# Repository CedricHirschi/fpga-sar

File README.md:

# FPGA-SAR

Material for the SAR ADC project in the **iCEBreaker FPGA For IoT Sensing Systems** FS2024 course.

## Project Description

Build a SAR ADC and a way to read its values.
- [x] Build analog part (See [hardware/](hardware/))
- [x] Develop SAR core (See [verilog/](verilog/))
- [x] Develop UART readout core (See [verilog/](verilog/))
- [ ] Optional: Evaluate speed and accuracy

## Project Structure

- [hardware/](hardware/): Contains the KiCad project for the analog part of the SAR ADC
- [verilog/](verilog/): Contains the Verilog code for the SAR ADC and UART readout core
- [gui.ipynb](gui.ipynb): Jupyter notebook for plotting the ADC values
- [activate.sh](activate.sh): Script to activate the virtual environment for development with APIO and Jupyter Notebook
- [presentation.pptx](presentation.pptx): Presentation slides for the project

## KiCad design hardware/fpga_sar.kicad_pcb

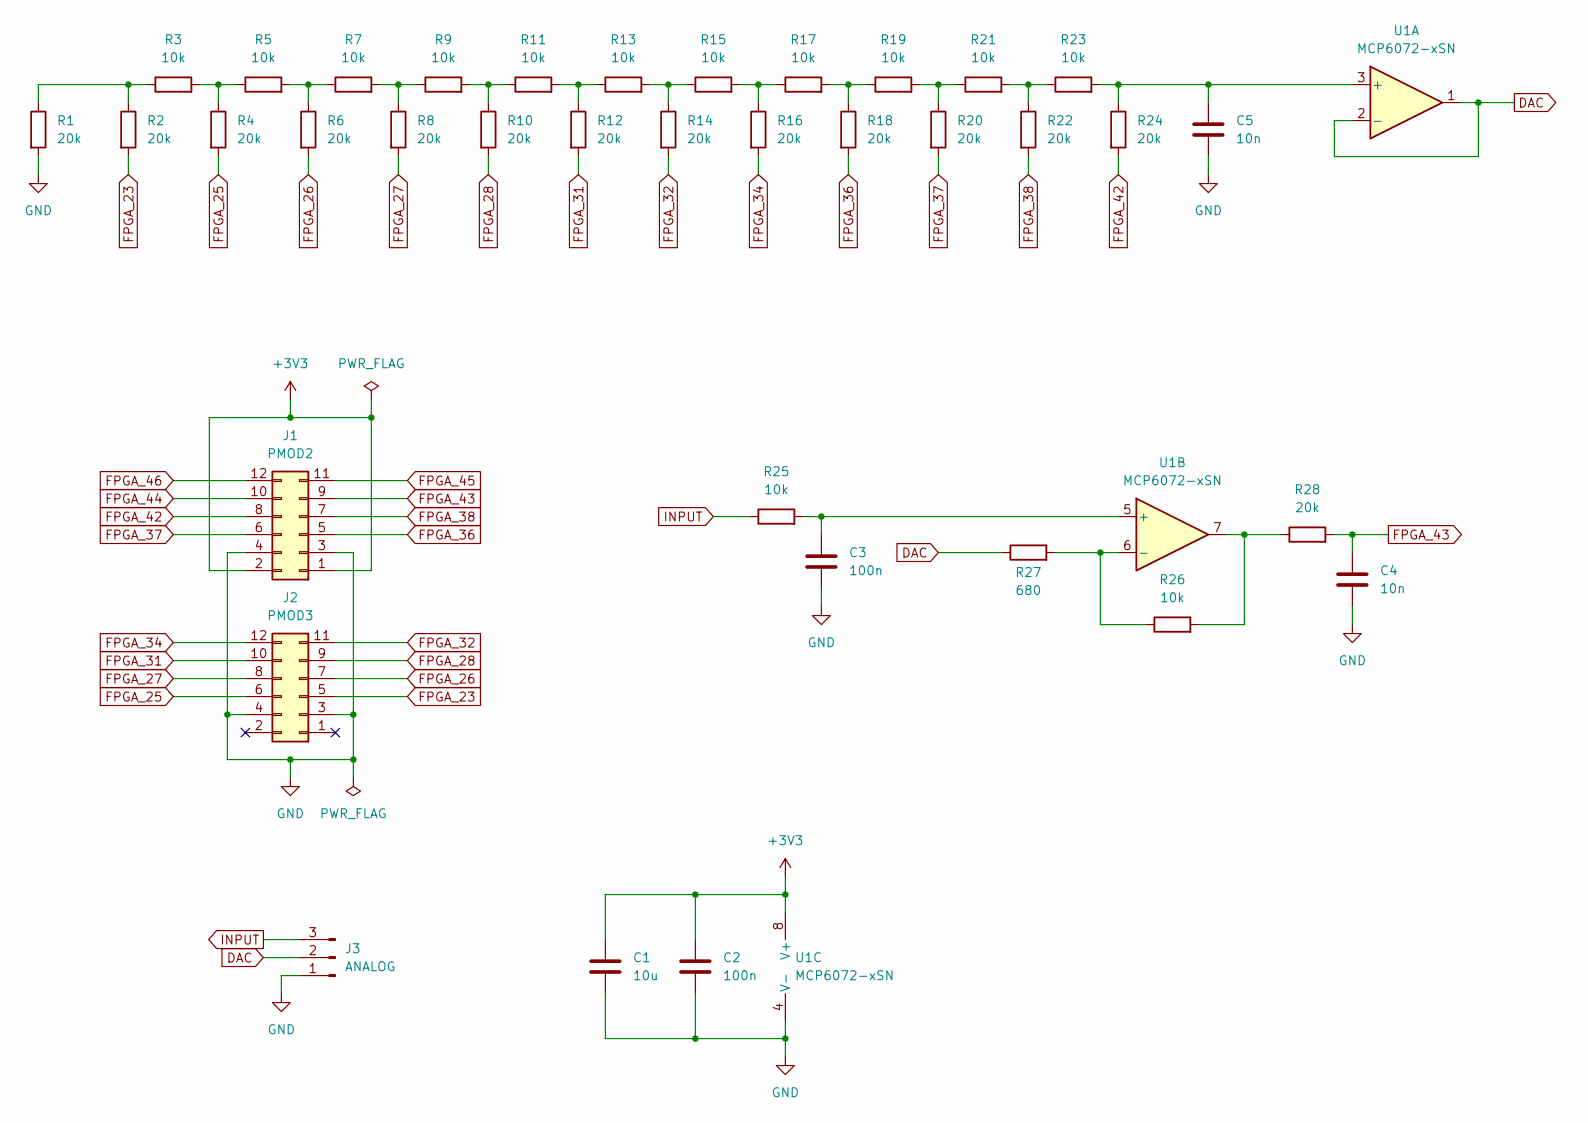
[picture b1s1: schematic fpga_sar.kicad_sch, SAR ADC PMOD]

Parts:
C1: 10u; C_0402_1005Metric
C2, C3: 100n; C_0402_1005Metric
C4, C5: 10n; C_0402_1005Metric
J1: PMOD2; PinHeader_2x06_P2.54mm_Horizontal
J2: PMOD3; PinHeader_2x06_P2.54mm_Horizontal
J3: ANALOG; PinHeader_1x03_P2.54mm_Vertical
R1, R2, R4, R6, R8, R10, R12, R14, R16, R18, R20, R22, R24, R28: 20k; R_0402_1005Metric
R3, R5, R7, R9, R11, R13, R15, R17, R19, R21, R23, R25, R26: 10k; R_0402_1005Metric
R27: 680; R_0402_1005Metric
U1: MCP6072-xSN; SOIC-8_3.9x4.9mm_P1.27mm

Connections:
+3V3: C1.1, C2.1, J1.1, J1.2, U1.8 (V+)
DAC: J3.2, R27.1, U1.1, U1.2 (-)
FPGA_23: J2.5, R2.2
FPGA_25: J2.6, R4.2
FPGA_26: J2.7, R6.2
FPGA_27: J2.8, R8.2
FPGA_28: J2.9, R10.2
FPGA_31: J2.10, R12.2
FPGA_32: J2.11, R14.2
FPGA_34: J2.12, R16.2
FPGA_36: J1.5, R18.2
FPGA_37: J1.6, R20.2
FPGA_38: J1.7, R22.2
FPGA_42: J1.8, R24.2
FPGA_43: C4.1, J1.9, R28.2
FPGA_44: J1.10
FPGA_45: J1.11
FPGA_46: J1.12
GND: C1.2, C2.2, C3.2, C4.2, C5.2, J1.3, J1.4, J2.3, J2.4, J3.1, R1.2, U1.4 (V-)
INPUT: J3.3, R25.1
unnamed: R1.1, R2.1, R3.1
unnamed: R3.2, R4.1, R5.1
unnamed: R5.2, R6.1, R7.1
unnamed: R7.2, R8.1, R9.1
unnamed: R9.2, R10.1, R11.1
unnamed: R11.2, R12.1, R13.1
unnamed: R13.2, R14.1, R15.1
unnamed: R15.2, R16.1, R17.1
unnamed: R17.2, R18.1, R19.1
unnamed: R19.2, R20.1, R21.1
unnamed: R21.2, R22.1, R23.1
unnamed: R26.2, R28.1, U1.7
unnamed: C5.1, R23.2, R24.1, U1.3 (+)
unnamed: C3.1, R25.2, U1.5 (+)
unnamed: R26.1, R27.2, U1.6 (-)

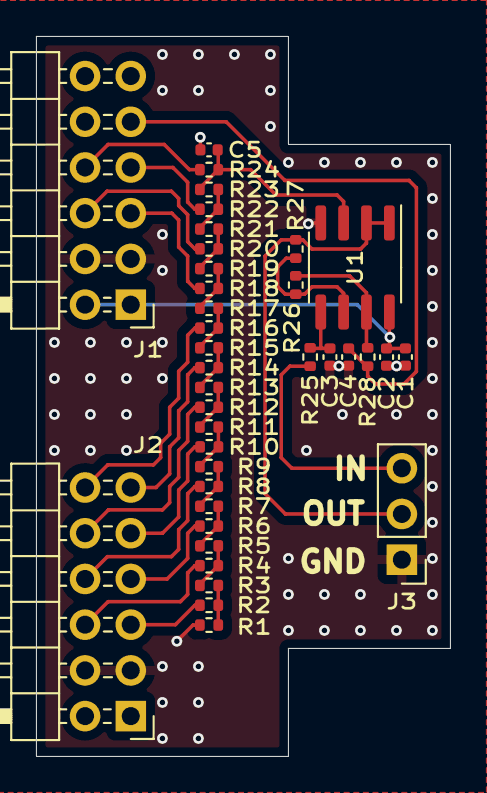
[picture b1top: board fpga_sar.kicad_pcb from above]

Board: 2 copper layers, 23.0 x 40.0 mm, 37 parts (0 on the bottom side), 32 nets.

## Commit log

2024-04-23 Initial version
    Conversion may show one below actual result
2024-04-24 Add UART readout
    Send 's' via UART 115200, 8 bits, 1 stop, no parity
2024-04-24 Add GUI notebook
2024-04-24 Add time plot
2024-04-25 Fix pinout for breakout
2024-04-25 Add parameters to main module
2024-04-25 Add minigame
2024-05-26 Preparation for presentation
2024-05-26 Add README.md
2024-05-26 Add Github link to presentation
